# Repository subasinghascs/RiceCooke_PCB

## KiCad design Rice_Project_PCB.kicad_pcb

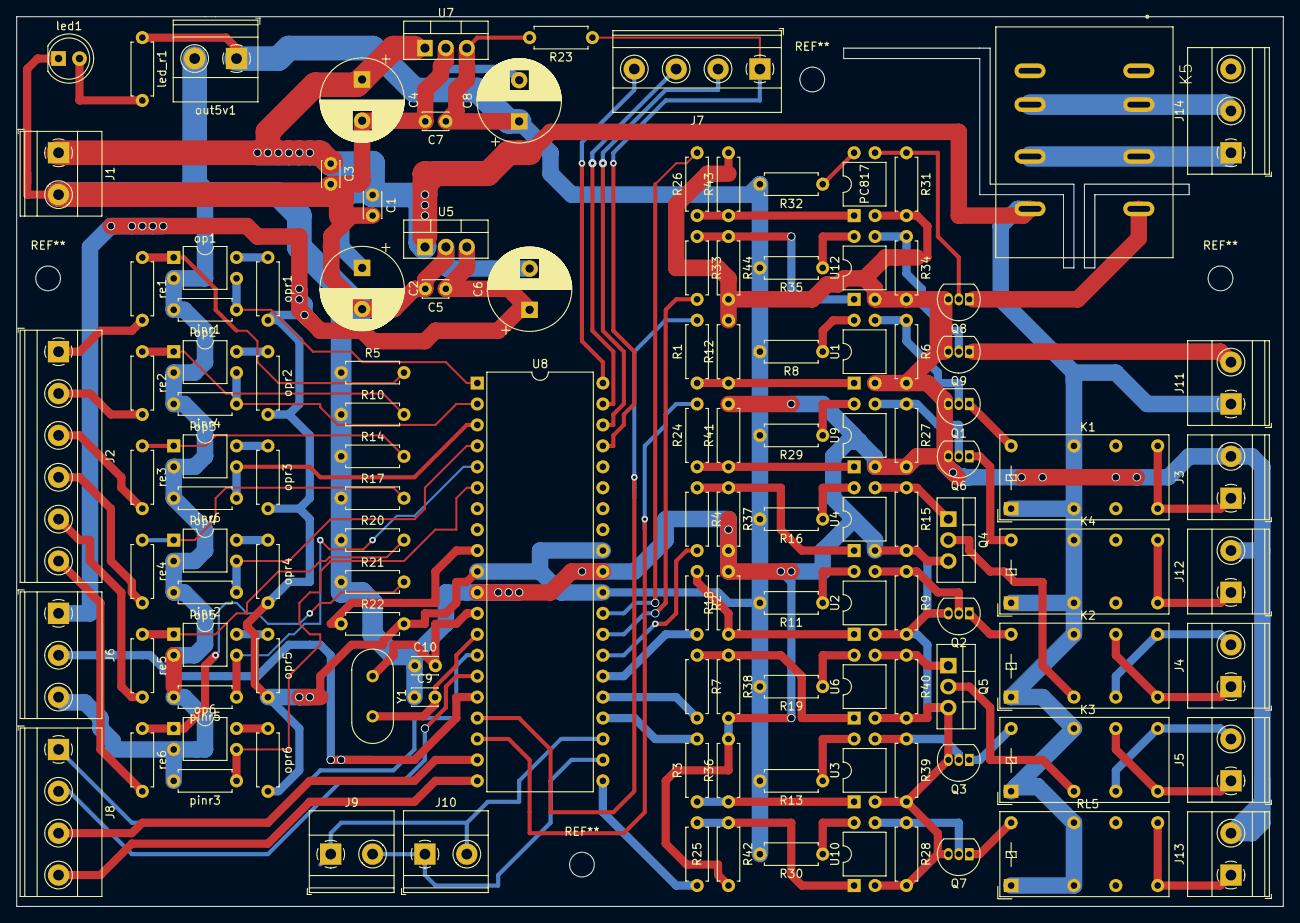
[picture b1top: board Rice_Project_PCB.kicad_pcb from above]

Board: 2 copper layers, 153.7 x 107.9 mm, 123 parts (0 on the bottom side), 96 nets.

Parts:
C1, C3, C5, C7: 104; C_Disc_D3.0mm_W2.0mm_P2.50mm
C2, C4, C6, C8: 220uf; CP_Radial_D10.0mm_P5.00mm
C9, C10: 22uf; C_Disc_D3.0mm_W2.0mm_P2.50mm
J1: INPUT; TerminalBlock_Phoenix_MKDS-1,5-2-5.08_1x02_P5.08mm_Horizont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
J2: Conn_01x06_Female; TerminalBlock_Phoenix_MKDS-1,5-6-5.08_1x06_P5.08mm_Horizont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
J3, J4, J5, J9, J10, J11, J12, J13: Conn_01x02_Female; TerminalBlock_Phoenix_MKDS-1,5-2-5.08_1x02_P5.08mm_Horizont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
J6, J14: Conn_01x03_Female; TerminalBlock_Phoenix_MKDS-1,5-3-5.08_1x03_P5.08mm_Horizont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
J7, J8: Conn_01x04_Female; TerminalBlock_Phoenix_MKDS-1,5-4-5.08_1x04_P5.08mm_Horizont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
K1, K2, K3, K4: FINDER-40.52; Relay_DPDT_Finder_30.22
K5: OMRON_MY2N
Q1, Q2, Q3, Q6, Q7, Q8, Q9: BC548; TO-92_Inline
Q4, Q5: IRF540N; TO-220-3_Vertical
R1, R2, R3, R4, R7, R8, R11, R12, R13, R22, R24, R25, R26, R29, R30, R32, R33, R35, R36, R38: 1k; R_Axial_DIN0207_L6.3mm_D2.5mm_P7.62mm_Horizontal
R5, R6, R9, R10, R14, R15, R17, R20, R21, R23, R27, R28, R31, R34, R39, R40: 10k; R_Axial_DIN0207_L6.3mm_D2.5mm_P7.62mm_Horizontal
R16, R19: 100; R_Axial_DIN0207_L6.3mm_D2.5mm_P7.62mm_Horizontal
R18, R37, R41, R42, R43, R44: R; R_Axial_DIN0207_L6.3mm_D2.5mm_P7.62mm_Horizontal
RL5: G2RL-2-ASI-DC12; Relay_DPDT_Finder_30.22
U1, U2, U3, U4, U6, U9, U10, U11, U12: PC817; DIP-4_W7.62mm
U5, U7: L7805; TO-220-3_Vertical
U8: ATmega32-16PU; DIP-40_W15.24mm
Y1: 16mhz; Crystal_HC49-4H_Vertical
led1: LED; LED_D5.0mm
led_r1: 470; R_Axial_DIN0207_L6.3mm_D2.5mm_P7.62mm_Horizontal
op1, op2, op3, op4, op5, op6: PC817; DIP-4_W7.62mm
opr1, opr2, opr3, opr4, opr5, opr6: 100; R_Axial_DIN0207_L6.3mm_D2.5mm_P7.62mm_Horizontal
out5v1: OUTPUT 5v; TerminalBlock_Phoenix_MKDS-1,5-2-5.08_1x02_P5.08mm_Horizont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
pinr1, pinr2, pinr3, pinr4, pinr5, pinr6: 10k; R_Axial_DIN0207_L6.3mm_D2.5mm_P7.62mm_Horizontal
re1, re2, re3, re4, re5, re6: 1k; R_Axial_DIN0207_L6.3mm_D2.5mm_P7.62mm_Horizontal

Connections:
5VCC: C5.1, C6.1, C7.1, C8.1, J6.1, R8.2, R11.2, R13.2, R16.2, R19.2, R22.2, R23.2, R29.2, R30.2, R32.2, R35.2, U5.3, U7.3, U8.10, U8.30, U8.32, led_r1.1, opr1.2, opr2.2, opr3.2, opr4.2, opr5.2, opr6.2, out5v1.1
12VCC: C1.1, C2.1, C3.1, C4.1, J1.1, J11.1, K1.11, K1.21, K1.A1, K2.21, K2.A1, K3.21, K3.A1, K4.11, K4.21, K4.A1, K5.14, RL5.11, RL5.21, RL5.A1, U5.1, U7.1
230live: J14.1, K5.9, K5.12
DOUT_PIN: J8.4, U8.20
GND: C1.2, C2.2, C3.2, C4.2, C5.2, C6.2, C7.2, C8.2, C9.1, C10.1, J1.2, J3.2, J6.3, J12.2, J13.2, Q1.3, Q2.3, Q3.3, Q4.3, Q5.3, Q6.3, Q7.3, Q8.3, Q9.3, R5.1, R6.2, R9.2, R10.1, R12.2, R14.1, R15.2, R17.1, R18.2, R20.1, R21.1, R27.2, R28.2, R31.2, R34.2, R36.2, R37.2, R38.2, R39.2, R40.2, R41.2, R42.2, R43.2, R44.2, U1.2, U2.2, U3.2, U4.2, U5.2, U6.2, U7.2, U8.11, U8.31, U9.2, U10.2, U11.2, U12.2, led1.1, op1.2, op2.2, op3.2, op4.2, op5.2, op6.2, out5v1.2, pinr1.2, pinr2.2, pinr3.2, pinr4.2, pinr5.2, pinr6.2
unnamed: J2.1, re1.2
unnamed: J2.2, re2.2
unnamed: J2.3, re3.2
unnamed: J2.4, re4.2
unnamed: J2.5, re5.2
unnamed: J2.6, re6.2
unnamed: J3.1, K1.14, K1.24
unnamed: J4.1, K2.14, K2.22
unnamed: J4.2, K2.12, K2.24
unnamed: J5.1, K3.14, K3.22
unnamed: J5.2, K3.12, K3.24
unnamed: J11.2, Q9.1
unnamed: J12.1, K4.14, K4.24
unnamed: J13.1, RL5.14, RL5.24
unnamed: J14.2, K5.5, K5.8
unnamed: K1.A2, Q1.1
unnamed: K2.11, Q4.2
unnamed: K2.A2, Q2.1
unnamed: K3.11, Q5.2
unnamed: K3.A2, Q3.1
unnamed: K4.A2, Q6.1
unnamed: K5.13, Q8.1
unnamed: Q1.2, R6.1, U1.3
unnamed: Q2.2, R9.1, U2.3
unnamed: Q3.2, R39.1, U3.3
unnamed: Q4.1, R15.1, U4.3
unnamed: Q5.1, R40.1, U6.3
unnamed: Q6.2, R27.1, U9.3
unnamed: Q7.1, RL5.A2
unnamed: Q7.2, R28.1, U10.3
unnamed: Q8.2, R31.1, U11.3
unnamed: Q9.2, R34.1, U12.3
unnamed: R1.1, R12.1, U1.1
unnamed: R3.1, R36.1, U3.1
unnamed: R5.2, op1.1, re1.1
unnamed: R8.1, U1.4
unnamed: R10.2, op2.1, re2.1
unnamed: R11.1, U2.4
unnamed: R13.1, U3.4
unnamed: R14.2, op3.1, re3.1
unnamed: R16.1, U4.4
unnamed: R17.2, op4.1, re4.1
unnamed: R2.1, R18.1, U2.1
unnamed: R19.1, U6.4
unnamed: R20.2, op5.1, re5.1
unnamed: R21.2, op6.1, re6.1
unnamed: R22.1, U8.9
unnamed: R24.1, R41.1, U9.1
unnamed: R25.1, R42.1, U10.1
unnamed: R26.1, R43.1, U11.1
unnamed: R29.1, U9.4
unnamed: R30.1, U10.4
unnamed: R32.1, U11.4
unnamed: R33.1, R44.1, U12.1
unnamed: R35.1, U12.4
unnamed: R4.1, R37.1, U4.1
unnamed: R7.1, R38.1, U6.1
unnamed: led1.2, led_r1.2
unnamed: op1.4, opr1.1
unnamed: op2.4, opr2.1
unnamed: op3.4, opr3.1
unnamed: op4.4, opr4.1
unnamed: op5.4, opr5.1
unnamed: op6.4, opr6.1
PD_SCK_PIN: J8.3, U8.19
Rx: J8.1, U8.14
SCL: J9.2, J10.1, U8.22
SDA: J9.1, J10.2, U8.23
Tx: J8.2, U8.15
XTL1: C9.2, U8.13, Y1.2
XTL2: C10.2, U8.12, Y1.1
buzzer_pin: R33.2, U8.28
cooker_lim_down: U8.3, op3.3, pinr6.1
cooker_lim_up: U8.4, op4.3, pinr2.1
cooker_set_lim: U8.5, op5.3, pinr5.1
dc_motor1: R3.2, U8.24
dc_motor1_derec: R7.2, U8.25
dc_motor2: R2.2, U8.26
dc_motor2_derec: R4.2, U8.27
echo_pin: J7.3, U8.39
finished_pin: U8.6, op6.3, pinr3.1
joystick_Y: J7.2, U8.38
joystick_ok: J7.1, R23.1, U8.37
ricecooker_on: R26.2, U8.29
servo_pin: J6.2, U8.16
solonid_in: R24.2, U8.18
solonid_out: R25.2, U8.21
trigger_pin: J7.4, U8.40
wash_lim_down: U8.1, op1.3, pinr1.1
wash_lim_up: U8.2, op2.3, pinr4.1
wash_motor_pin: R1.2, U8.17

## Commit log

2022-06-06 pcb final
